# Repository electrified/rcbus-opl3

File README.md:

# RCBus OPL3 Sound card

An OPL3 sound card for RC2014/RCBus based computers, based on the Yamaha YMF262 and YAC512 ICs.

## Building the board
A site built from the sources is available https://electrified.github.io/rcbus-opl3-site. For Gerbers to get your own PCB manufactured see here, download the most appropriate zip for your PCB manufacturer: https://electrified.github.io/rcbus-opl3-site/Browse/rcbus-opl3-navigate_PCB_fabrication_gerber.html

### BOM
The BOM for the board is available here https://electrified.github.io/rcbus-opl3-site/Browse/rcbus-opl3-navigate_Schematic_BoM.html. The CSV version can be loaded into sites that have BOM upload functionality.

## Configuration
The base address the card is available at is configured with JP1 - the default setting which VGMPLAY expects is **0x90** - place jumpers on the 10 and 80 rows to achieve this

## VGM playback
A lightly altered version of Marco Maccaferri and J.B. Langston's CP/M VGMPLAY is available [here](https://github.com/electrified/vgmplay). This allows playback of VGM files containing OPL2 and OPL3 content.

### Sources of OPL2/OPL3 VGM music
[OPL Archive](https://opl.wafflenet.com/#AmigaX)  
OPL3 Archive zip [from this page](https://roudoudou.com/ACE-DL/) - files are names in 8.3 format  
[VGMRips OPL2](https://vgmrips.net/packs/chip/ym3812)  
[VGMRips OPL3](https://vgmrips.net/packs/chip/ymf262)  
[VGMRips full download packs](https://vgmrips.net/forum/viewtopic.php?t=496)  

## Known issues with rev 1 (tick indicates fixed in R2)
- [x] YMF footprint too narrow
- [x] 10uf cap footprints too large
- [x] Pin 1 not indicated for oscillator
- [] Noise on startup before reset?
- [x] Cutout for line out isn't quite deep enough for the jack to sit flush without removing a bit of the plastic

## Developer notes
If you are modifying the Kicad design ensure you have the Exo font installed - it's in this repo in the `kibot_resources/fonts` directory.

## Sponsorship
The first run of prototype PCBs was kindly provided by [PCBWay](https://www.pcbway.com/)! This was the first time I used their service, and I have been impressed with the process and the quality of the boards. I opted for purple boards with a HASL finish - the soldermask is quite opaque, it's a nice finish though and the quality of the boards is high. They also managed to put their serial number / identifier under an IC footprint so it's nicely concealed which not all the board houses manage!

A stencil was ordered to go along with the PCB to allow solder paste to be used and to do reflow soldering on a hotplate - this worked well. 

I opted for the cheapest post option, and it was still pretty speedy to the UK, I'm not sure I'd bother paying for one of the more expensive options unless I was really in a rush.

## License
RCBus OPL3 Sound Card ©2025 by Ed Brindley is licensed under CC BY-SA 4.0. To view a copy of this license, visit https://creativecommons.org/licenses/by-sa/4.0/

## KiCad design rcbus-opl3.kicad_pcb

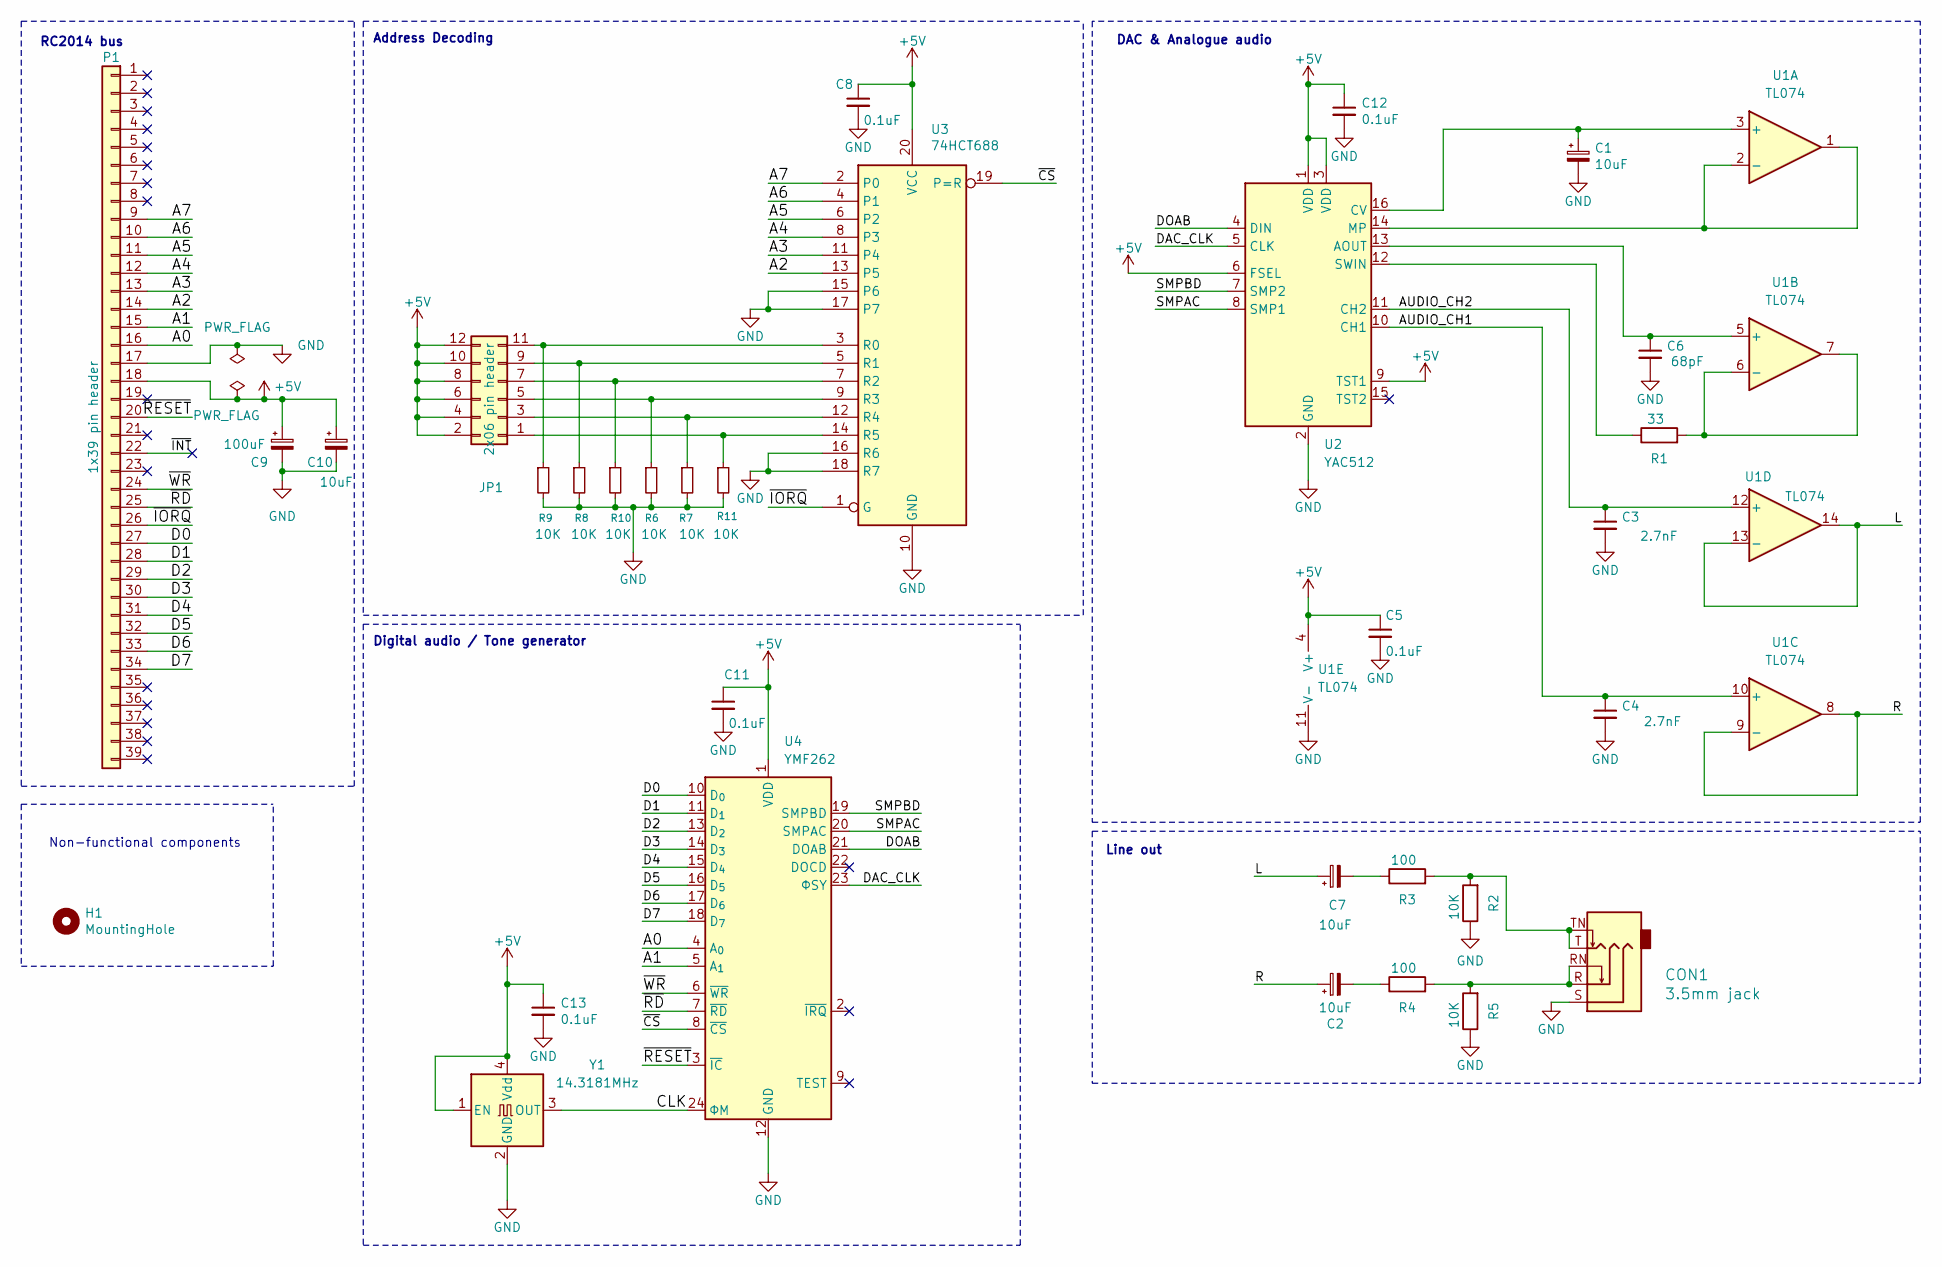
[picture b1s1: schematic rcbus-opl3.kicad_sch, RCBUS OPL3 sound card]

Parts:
C1, C2, C7, C10: 10uF; CP_Elec_4x5.4; MPN EDK106M035A9BAA
C3, C4: 2.7nF; C_0603_1608Metric; MPN MC0603N272J500CT
C5, C8, C11, C12, C13: 0.1uF; C_0603_1608Metric; MPN MC0603B104M250CT
C6: 68pF; C_0603_1608Metric; MPN MC0603N680J500CT
C9: 100uF; CP_Elec_6.3x7.7; MPN EDK107M035A9HAA
CON1: 3.5mm jack; Headphone_Jack_3.5mm_5_pin; MPN FC68131
H1: MountingHole; MountingHole_3.2mm_M3
JP1: 2x06 pin header; PinHeader_2x06_P2.54mm_Vertical; MPN M20-9980346
P1: 1x39 pin header; PinHeader_1x39_P2.54mm_Vertical; MPN 61304011021
R1: 33; R_0603_1608Metric; MPN MCWR06X33R0FTL
R2, R5, R6, R7, R8, R9, R10, R11: 10K; R_0603_1608Metric; MPN MCWR06X1002FTL
R3, R4: 100; R_0603_1608Metric; MPN MCWR06X1000FTL
U1: TL074; SOIC-14_3.9x8.7mm_P1.27mm; MPN TL074CDT
U2: YAC512; SOP-16_4.55x10.3mm_P1.27mm
U3: 74HCT688; SOIC-20W_7.5x12.8mm_P1.27mm; MPN CD74HCT688M96
U4: YMF262; SOP-24_wider
Y1: 14.3181MHz; Oscillator_SMD_Abracon_ASV-4Pin_7.0x5.1mm; MPN MCSJK-6NC1-14.31818-25-B

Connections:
+5V: C5.1, C8.1, C9.1, C10.1, C11.1, C12.1, C13.1, JP1.2, JP1.4, JP1.6, JP1.8, JP1.10, JP1.12, P1.18, U1.4 (V+), U2.1 (VDD), U2.3 (VDD), U2.6 (FSEL), U2.9 (TST1), U3.20 (VCC), U4.1 (VDD), Y1.1 (EN), Y1.4 (Vdd)
/A0: P1.16, U4.4 (A_{0})
/A1: P1.15, U4.5 (A_{1})
/A2: P1.14, U3.13 (P5)
/A3: P1.13, U3.11 (P4)
/A4: P1.12, U3.8 (P3)
/A5: P1.11, U3.6 (P2)
/A6: P1.10, U3.4 (P1)
/A7: P1.9, U3.2 (P0)
/AUDIO_CH1: C4.1, U1.10 (+), U2.10 (CH1)
/AUDIO_CH2: C3.1, U1.12 (+), U2.11 (CH2)
/CLK: U4.24 (ΦM), Y1.3 (OUT)
/D0: P1.27, U4.10 (D_{0})
/D1: P1.28, U4.11 (D_{1})
/D2: P1.29, U4.13 (D_{2})
/D3: P1.30, U4.14 (D_{3})
/D4: P1.31, U4.15 (D_{4})
/D5: P1.32, U4.16 (D_{5})
/D6: P1.33, U4.17 (D_{6})
/D7: P1.34, U4.18 (D_{7})
/DAC_CLK: U2.5 (CLK), U4.23 (ΦSY)
/DOAB: U2.4 (DIN), U4.21 (DOAB)
/L: C7.1, U1.13 (-), U1.14
/R: C2.1, U1.8, U1.9 (-)
/SMPAC: U2.8 (SMP1), U4.20 (SMPAC)
/SMPBD: U2.7 (SMP2), U4.19 (SMPBD)
/~CS: U3.19 (P=R), U4.8 (~CS)
/~INT: P1.22
/~IORQ: P1.26, U3.1 (G)
/~RD: P1.25, U4.7 (~RD)
/~RESET: P1.20, U4.3 (~IC)
/~WR: P1.24, U4.6 (~WR)
GND: C1.2, C3.2, C4.2, C5.2, C6.2, C8.2, C9.2, C10.2, C11.2, C12.2, C13.2, CON1.S, P1.17, R2.1, R5.1, R6.2, R7.2, R8.2, R9.2, R10.2, R11.2, U1.11 (V-), U2.2 (GND), U3.10 (GND), U3.15 (P6), U3.16 (R6), U3.17 (P7), U3.18 (R7), U4.12 (GND), Y1.2 (GND)
unnamed: C2.2, R4.1
unnamed: C7.2, R3.1
unnamed: CON1.R, CON1.RN, R4.2, R5.2
unnamed: CON1.T, CON1.TN, R2.2, R3.2
unnamed: JP1.1, R11.1, U3.14 (R5)
unnamed: JP1.3, R7.1, U3.12 (R4)
unnamed: JP1.5, R6.1, U3.9 (R3)
unnamed: JP1.7, R10.1, U3.7 (R2)
unnamed: JP1.9, R8.1, U3.5 (R1)
unnamed: JP1.11, R9.1, U3.3 (R0)
unnamed: C1.1, U1.3 (+), U2.16 (CV)
unnamed: U1.1, U1.2 (-), U2.14 (MP)
unnamed: C6.1, U1.5 (+), U2.13 (AOUT)
unnamed: R1.2, U1.6 (-), U1.7
unnamed: R1.1, U2.12 (SWIN)

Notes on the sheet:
Non-functional components
Line out
Digital audio / Tone generator
Address Decoding
DAC & Analogue audio
RC2014 bus

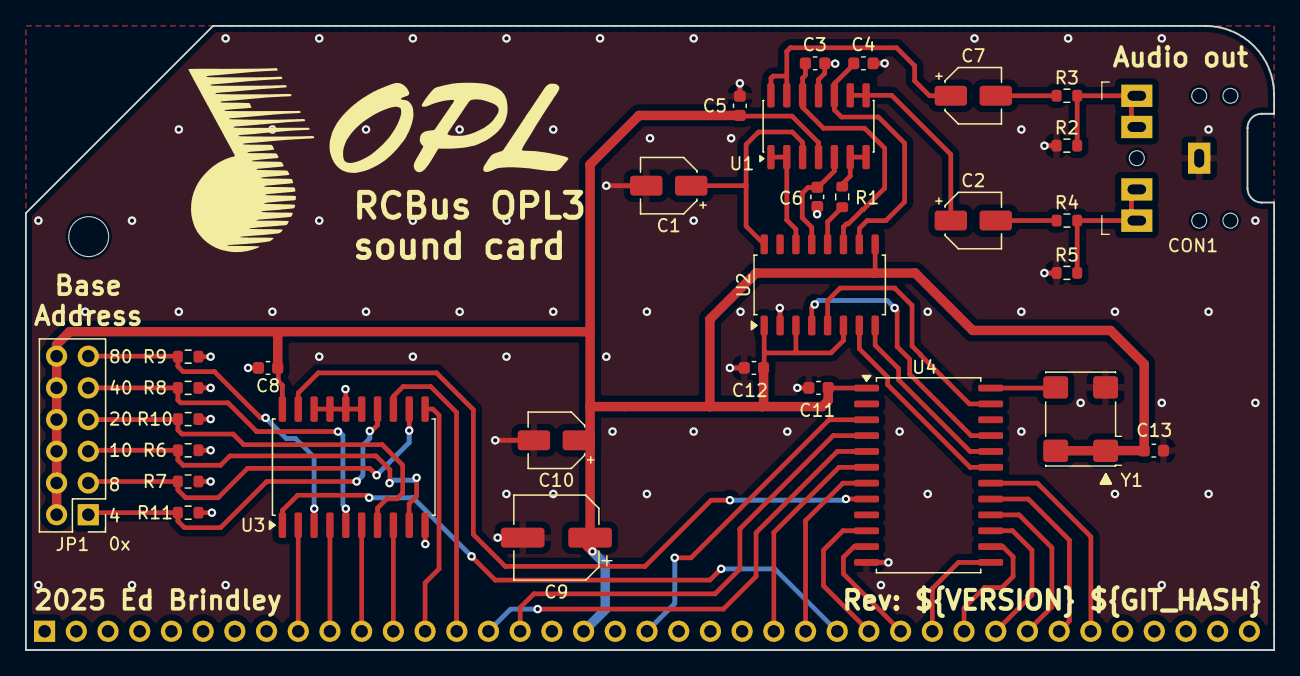
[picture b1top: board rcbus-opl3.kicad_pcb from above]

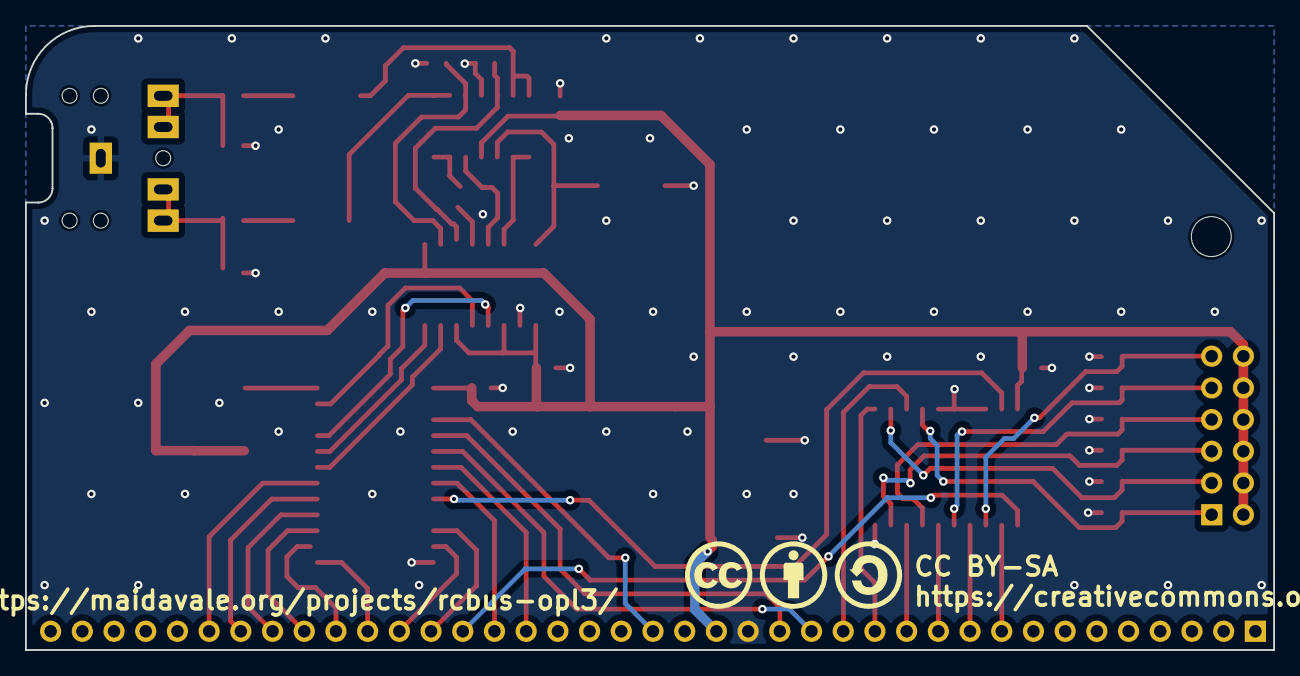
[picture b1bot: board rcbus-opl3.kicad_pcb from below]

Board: 2 copper layers, 100.0 x 50.0 mm, 38 parts (3 on the bottom side), 47 nets.

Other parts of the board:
G1: LOGO; adlib2
G2: LOGO; opl
G3: Symbol_CreativeCommons_Silk_Type2_Small
G4: Symbol_CC-Attribution_Silk_Small
G5: Symbol_CC-ShareAlike_Silk_Small

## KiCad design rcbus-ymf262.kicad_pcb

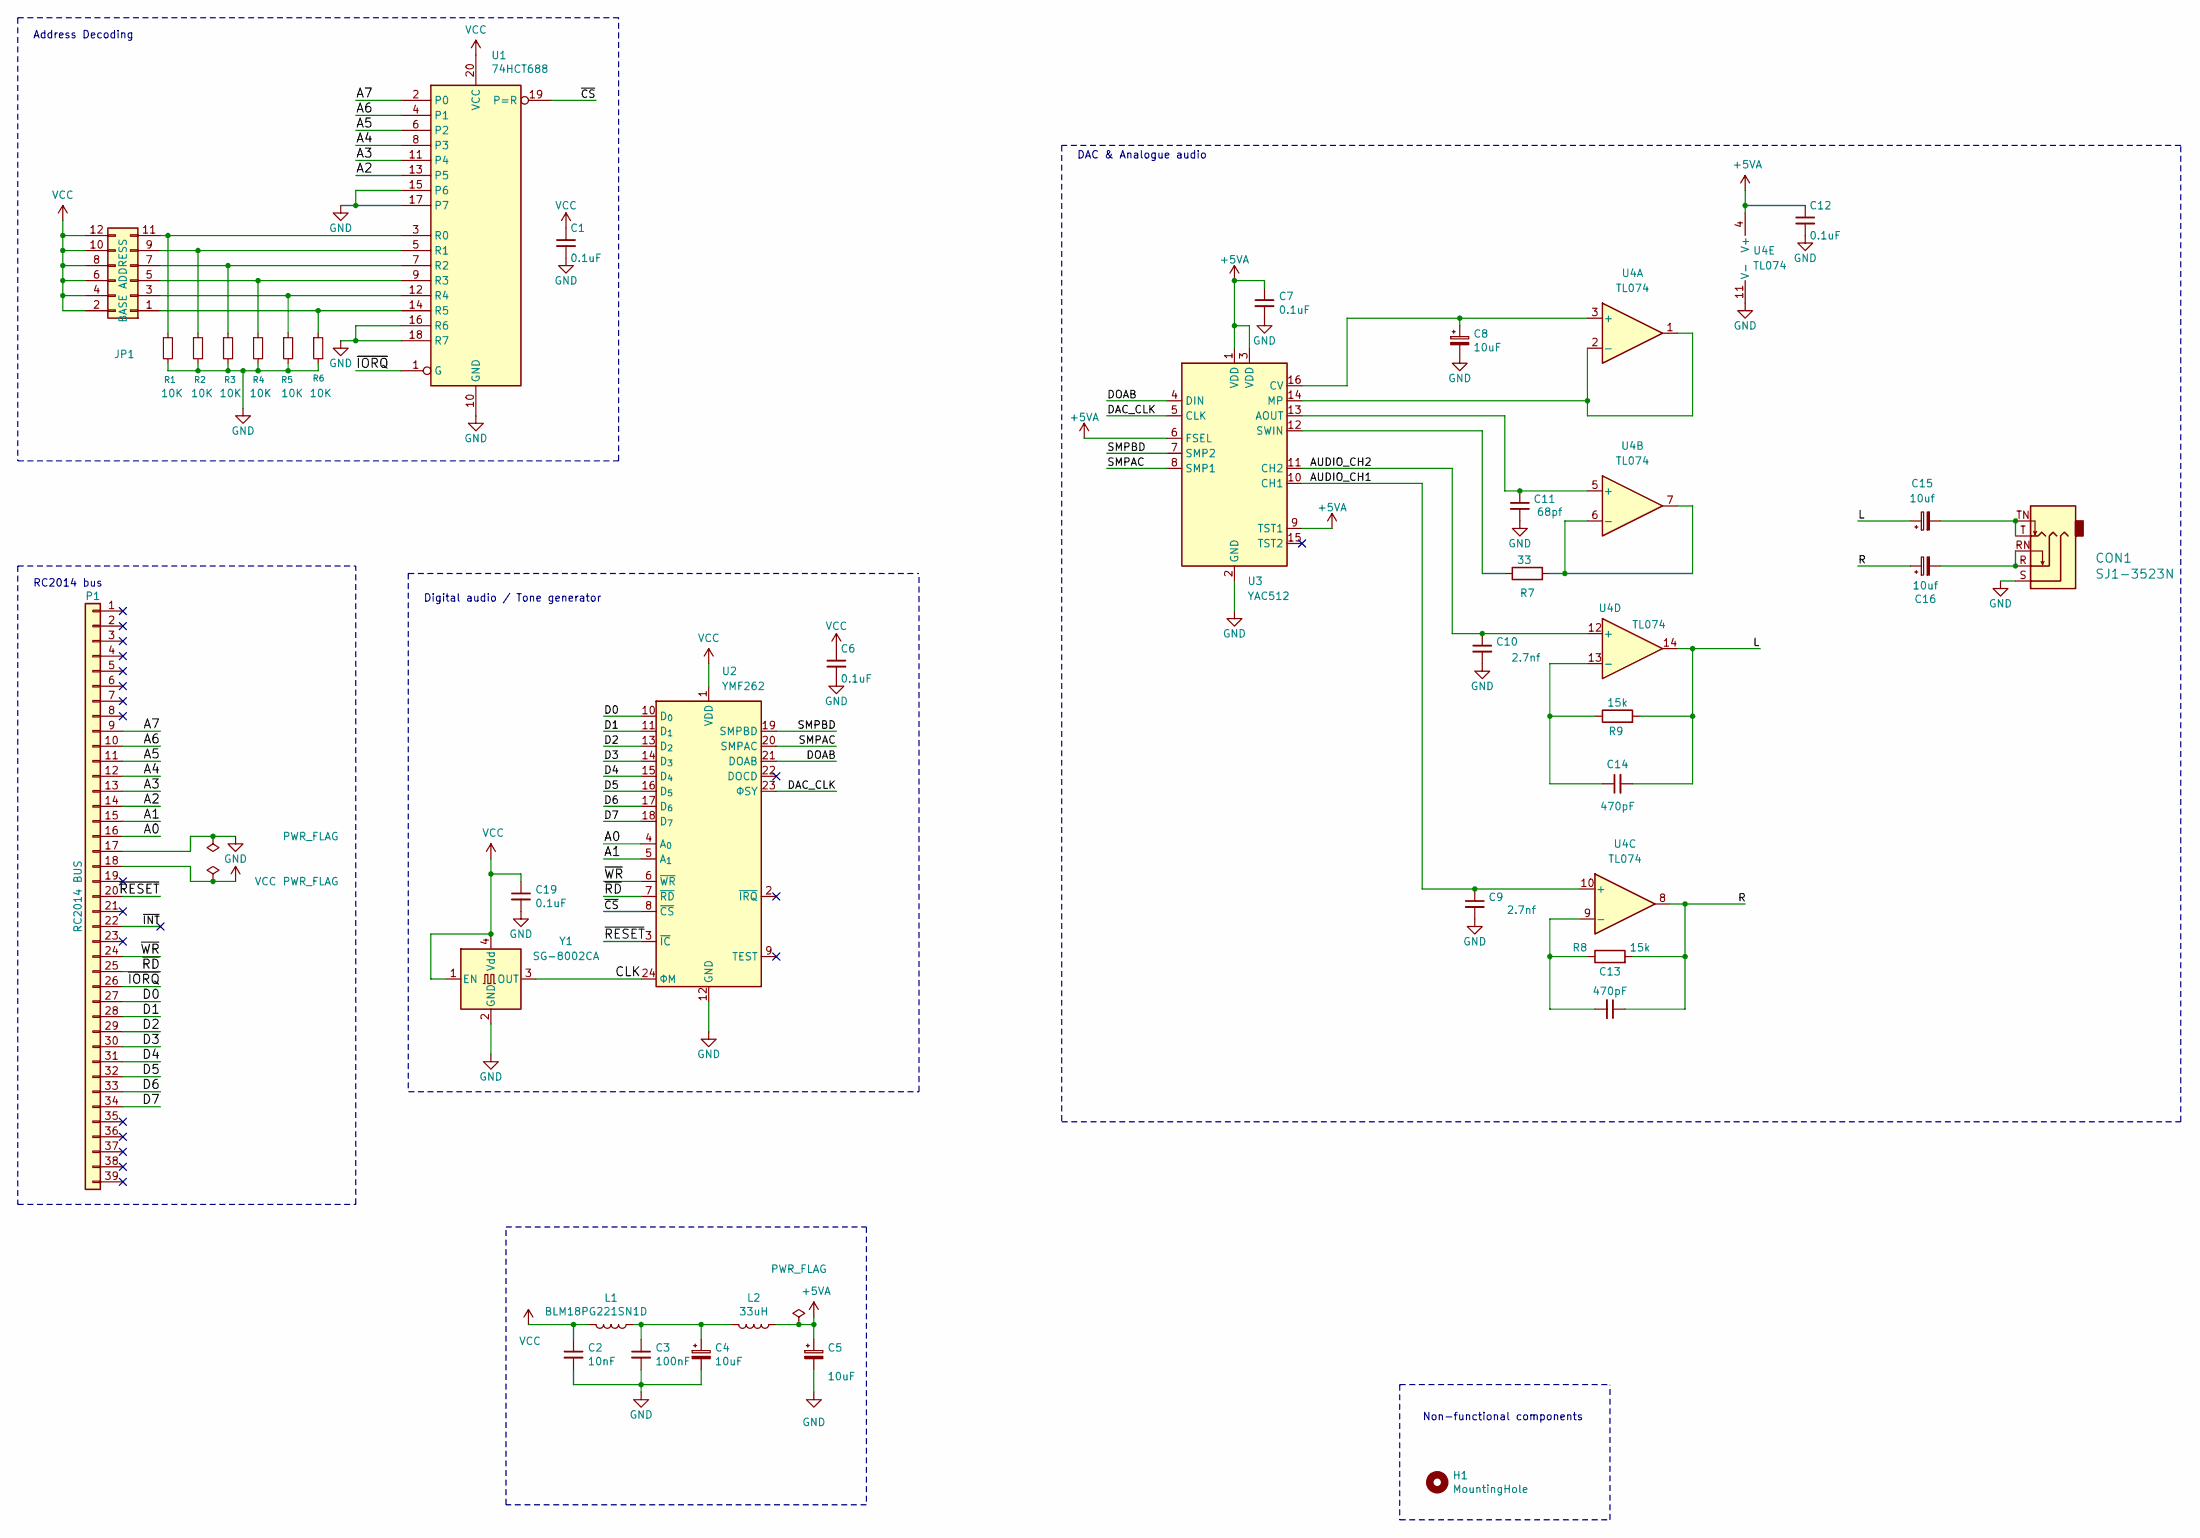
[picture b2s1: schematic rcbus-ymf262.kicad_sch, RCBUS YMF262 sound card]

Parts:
C1, C6, C7, C12, C19: 0.1uF; C_0603_1608Metric
C2: 10nF; C_0603_1608Metric
C3: 100nF; C_0603_1608Metric
C4, C5: 10uF; C_1206_3216Metric
C8: 10uF; C_0603_1608Metric
C9, C10: 2.7nf; C_0603_1608Metric
C11: 68pf; C_0603_1608Metric
C13, C14: 470pF; C_0603_1608Metric
C15, C16: 10uf; C_1206_3216Metric
CON1: SJ1-3523N; Headphone_Jack_3.5mm_5_pin; MPN SJ1-3523N; Digi-Key_PN CP1-3523N-ND
H1: MountingHole; MountingHole_3.2mm_M3
JP1: BASE ADDRESS; PinHeader_2x06_P2.54mm_Vertical
L1: BLM18PG221SN1D; L_0603_1608Metric
L2: 33uH; L_0603_1608Metric
P1: RC2014 BUS; PinHeader_1x39_P2.54mm_Vertical
R1, R2, R3, R4, R5, R6: 10K; R_0603_1608Metric
R7: 33; R_0603_1608Metric
R8, R9: 15k; R_0603_1608Metric
U1: 74HCT688; SOIC-20W_7.5x12.8mm_P1.27mm
U2: YMF262; SOP-24_7.5x15.4mm_P1.27mm
U3: YAC512; SOP-16_4.55x10.3mm_P1.27mm
U4: TL074; SOIC-14_3.9x8.7mm_P1.27mm
Y1: SG-8002CA; Oscillator_SMD_Abracon_ASV-4Pin_7.0x5.1mm

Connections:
+5VA: C5.1, C7.1, C12.1, L2.1, U3.1 (VDD), U3.3 (VDD), U3.6 (FSEL), U3.9 (TST1), U4.4 (V+)
/A0: P1.16, U2.4 (A_{0})
/A1: P1.15, U2.5 (A_{1})
/A2: P1.14, U1.13 (P5)
/A3: P1.13, U1.11 (P4)
/A4: P1.12, U1.8 (P3)
/A5: P1.11, U1.6 (P2)
/A6: P1.10, U1.4 (P1)
/A7: P1.9, U1.2 (P0)
/AUDIO_CH1: C9.1, U3.10 (CH1), U4.10 (+)
/AUDIO_CH2: C10.1, U3.11 (CH2), U4.12 (+)
/CLK: U2.24 (ΦM), Y1.3 (OUT)
/D0: P1.27, U2.10 (D_{0})
/D1: P1.28, U2.11 (D_{1})
/D2: P1.29, U2.13 (D_{2})
/D3: P1.30, U2.14 (D_{3})
/D4: P1.31, U2.15 (D_{4})
/D5: P1.32, U2.16 (D_{5})
/D6: P1.33, U2.17 (D_{6})
/D7: P1.34, U2.18 (D_{7})
/DAC_CLK: U2.23 (ΦSY), U3.5 (CLK)
/DOAB: U2.21 (DOAB), U3.4 (DIN)
/L: C14.2, C15.1, R9.2, U4.14
/R: C13.1, C16.1, R8.2, U4.8
/SMPAC: U2.20 (SMPAC), U3.8 (SMP1)
/SMPBD: U2.19 (SMPBD), U3.7 (SMP2)
/~CS: U1.19 (P=R), U2.8 (~CS)
/~INT: P1.22
/~IORQ: P1.26, U1.1 (G)
/~RD: P1.25, U2.7 (~RD)
/~RESET: P1.20, U2.3 (~IC)
/~WR: P1.24, U2.6 (~WR)
GND: C1.2, C2.2, C3.2, C4.2, C5.2, C6.2, C7.2, C8.2, C9.2, C10.2, C11.2, C12.2, C19.2, CON1.S, P1.17, R1.2, R2.2, R3.2, R4.2, R5.2, R6.2, U1.10 (GND), U1.15 (P6), U1.16 (R6), U1.17 (P7), U1.18 (R7), U2.12 (GND), U3.2 (GND), U4.11 (V-), Y1.2 (GND)
unnamed: C3.1, C4.1, L1.1, L2.2
unnamed: C15.2, CON1.T, CON1.TN
unnamed: C16.2, CON1.R, CON1.RN
unnamed: JP1.1, R6.1, U1.14 (R5)
unnamed: JP1.3, R5.1, U1.12 (R4)
unnamed: JP1.5, R4.1, U1.9 (R3)
unnamed: JP1.7, R3.1, U1.7 (R2)
unnamed: JP1.9, R2.1, U1.5 (R1)
unnamed: JP1.11, R1.1, U1.3 (R0)
unnamed: C11.1, U3.13 (AOUT), U4.5 (+)
unnamed: C8.1, U3.16 (CV), U4.3 (+)
unnamed: U3.14 (MP), U4.1, U4.2 (-)
unnamed: R7.1, U3.12 (SWIN)
unnamed: R7.2, U4.6 (-), U4.7
unnamed: C13.2, R8.1, U4.9 (-)
unnamed: C14.1, R9.1, U4.13 (-)
VCC: C1.1, C2.1, C6.1, C19.1, JP1.2, JP1.4, JP1.6, JP1.8, JP1.10, JP1.12, L1.2, P1.18, U1.20 (VCC), U2.1 (VDD), Y1.1 (EN), Y1.4 (Vdd)

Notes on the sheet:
Non-functional components
Digital audio / Tone generator
Address Decoding
DAC & Analogue audio
RC2014 bus

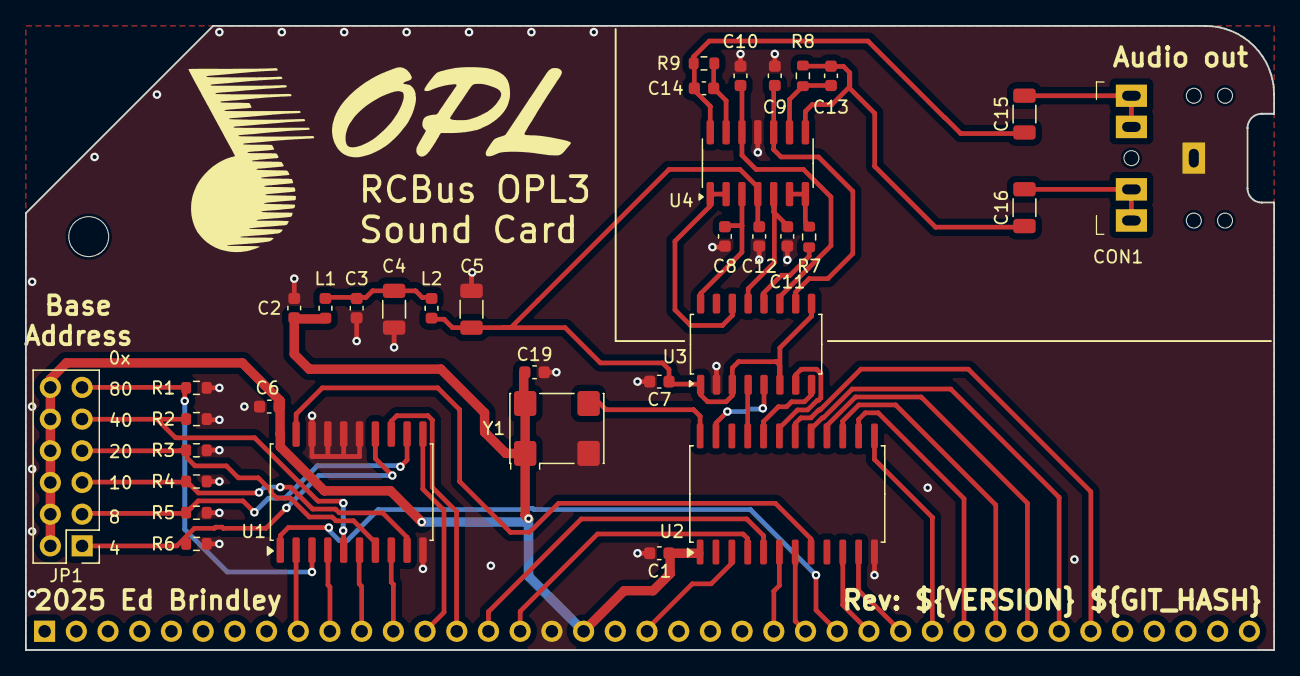
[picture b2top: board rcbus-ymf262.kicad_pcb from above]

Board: 2 copper layers, 100.0 x 50.0 mm, 39 parts (0 on the bottom side), 49 nets.

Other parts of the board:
G1: LOGO; adlib2
G2: LOGO; opl

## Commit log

2025-07-22 initial commit
    wip
2025-07-22 initial work on schematic
2025-07-23 move to use mostly SMD
2025-07-24 use custom oscillator footprint
2025-08-04 more work on schematic and layout
2025-08-05 add test program
2025-08-15 add additional docs and other random updates
2025-08-16 some more routing, use individual resistors, change name to rcbus
2025-08-17 fully routed - first attempt
2025-08-17 move some vias out of pads
2025-08-17 reroute
2025-08-18 Bump actions/checkout from 4 to 5 in the actions-dependencies group
    Bumps the actions-dependencies group with 1 update: [actions/checkout](https://github.com/actions/checkout).
    Updates `actions/checkout` from 4 to 5
    - [Release notes](https://github.com/actions/checkout/releases)
    - [Changelog](https://github.com/actions/checkout/blob/main/CHANGELOG.md)
    - [Commits](https://github.com/actions/checkout/compare/v4...v5)
    ---
2025-08-19 more routing
2025-08-20 pcb updates, remove old github actions
2025-08-20 add new kibot config
2025-08-20 do a git submodule update in action
2025-08-21 use updated footprints, update library submodule
2025-08-26 use smd oscillator
2025-08-28 set version no
2025-08-28 more versioning stuff
2025-08-31 remove gnda, another attempt at versioning
2025-09-01 another go at versioning
2025-09-01 more kibot work
2025-09-02 replace with quick start config
2025-09-02 comment out some kibot steps
2025-09-02 more kibot updates
2025-09-02 update library
2025-09-03 reorg
2025-09-11 some pcb tidyup, use netcallses for track widths
2025-09-12 update logo
2025-09-20 update url
2025-09-20 further silkscreen tidyups
2025-09-21 remove some components, more tidyup
2025-09-23 rename to rcbus-opl3
2025-09-23 add manual dispatch
2025-09-23 try and fix diff
2025-09-24 remove unneeded components, some layour rejigging
2025-09-26 add additional output caps/ resistors
2025-09-29 Bump the actions-dependencies group with 2 updates
    Bumps the actions-dependencies group with 2 updates: [actions/checkout](https://github.com/actions/checkout) and [actions/download-artifact](https://github.com/actions/download-artifact).
    Updates `actions/checkout` from 4 to 5
    - [Release notes](https://github.com/actions/checkout/releases)
    - [Changelog](https://github.com/actions/checkout/blob/main/CHANGELOG.md)
    - [Commits](https://github.com/actions/checkout/compare/v4...v5)
    Updates `actions/download-artifact` from 4 to 5
2025-10-01 remove some unusted stuff from kibot, update schematic and pcb
2025-10-02 as submitted for design review on reddit
2025-10-04 use gitignore from https://github.com/github/gitignore/blob/main/KiCad.gitignore
2025-10-04 reroute. add additional bulk cap
2025-10-05 rotate u2
2025-10-06 increase spacing between tracks, remove opl4 pdf
2025-10-07 remove 5v pour
2025-10-08 add cc logos and some tidyup
2025-10-09 add stitching vias
2025-10-09 more tidyup
2025-10-09 tidy up text
2025-10-10 sync up pcb and schematic, minor schematic tidyups
2025-10-10 attempt at uploading a release
2025-10-10 only release on tags
2025-10-11 remove some outputs from the kibot settings
2025-10-11 update some part fields
2025-10-12 add datasheets / farnell links
2025-10-12 update the parts for the large caps
2025-10-13 add mpn field
2025-10-13 update readme and kibot config
2025-10-26 some r2 changes
2025-11-02 update url in readme
2025-11-02 wip: change 10uf electrolytics to 4mm diameter, and use custom footprint for ymf262
2025-11-10 Bump the actions-dependencies group with 2 updates
    Bumps the actions-dependencies group with 2 updates: [actions/upload-artifact](https://github.com/actions/upload-artifact) and [actions/download-artifact](https://github.com/actions/download-artifact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
    Updates `actions/upload-artifact` from 4 to 5
    - [Release notes](https://github.com/actions/upload-artifact/releases)
    - [Commits](https://github.com/actions/upload-artifact/compare/v4...v5)
    Updates `actions/download-artifact` from 5 to 6
    - [Release notes](https://github.com/actions/download-artifact/releases)
2025-11-10 fix drc, reroute for new width components, add pin 1 indicator for oscillator
2025-11-24 Bump the actions-dependencies group across 1 directory with 3 updates
    Bumps the actions-dependencies group with 3 updates in the / directory: [actions/checkout](https://github.com/actions/checkout), [actions/upload-artifact](https://github.com/actions/upload-artifact) 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
    Updates `actions/checkout` from 5 to 6
    - [Release notes](https://github.com/actions/checkout/releases)
    - [Changelog](https://github.com/actions/checkout/blob/main/CHANGELOG.md)
    - [Commits](https://github.com/actions/checkout/compare/v5...v6)
    Updates `actions/upload-artifact` from 4 to 5
2026-01-02 update symbols/footprints to kicad 9.0.7, improve ymf footprint
2026-01-12 Bump the actions-dependencies group with 2 updates
    Bumps the actions-dependencies group with 2 updates: [actions/upload-artifact](https://github.com/actions/upload-artifact) and [actions/download-artifact](https://github.com/actions/download-artifact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
    Updates `actions/upload-artifact` from 5 to 6
    - [Release notes](https://github.com/actions/upload-artifact/releases)
    - [Commits](https://github.com/actions/upload-artifact/compare/v5...v6)
    Updates `actions/download-artifact` from 6 to 7
    - [Release notes](https://github.com/actions/download-artifact/releases)
2026-01-24 update actions
2026-01-24 Bump actions/upload-artifact
    Bumps the actions-dependencies group with 1 update in the / directory: [actions/upload-artifact](https://github.com/actions/upload-artifact).
    Updates `actions/upload-artifact` from 5 to 6
    - [Release notes](https://github.com/actions/upload-artifact/releases)
    - [Commits](https://github.com/actions/upload-artifact/compare/v5...v6)
    ---
    updated-dependencies:
2026-01-25 update actions
    change pipeline
    change pipeline
2026-01-25 Bump the actions-dependencies group across 1 directory with 2 updates
    Bumps the actions-dependencies group with 2 updates in the / directory: [actions/upload-artifact](https://github.com/actions/upload-artifact) and [actions/download-artifact](https://github.com/action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
    Updates `actions/upload-artifact` from 5 to 6
    - [Release notes](https://github.com/actions/upload-artifact/releases)
    - [Commits](https://github.com/actions/upload-artifact/compare/v5...v6)
    Updates `actions/download-artifact` from 6 to 7
    - [Release notes](https://github.com/actions/download-artifact/releases)
